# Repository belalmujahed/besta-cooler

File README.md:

# Bestå cooler

Closed-door cooling and lighting for a wall-mounted 3-bay IKEA Bestå TV unit: floor-mounted PWM fans in printed cassettes, one ESP32-C3 controller per bay, ESPHome firmware.

```
cad/        SolidCraft models + STL/STEP exports
  cassette/   fan flange + bottom scoop (one design, all bays)   ✅ v1
  baffle/     under-unit recirculation baffle                     ⏳
  ps5-riser/  platform lifting the PS5 over its fans              ⏳
  controller-case/ printed enclosure, all connectors outside       ✅ v1
pcb/        KiCad 10 project (controller, built 3×)  schematic ✅  layout ✅ (routed, DRC clean)
firmware/   ESPHome: one YAML + per-bay substitutions             ⏳
docs/       spec notes, pin map, BOM, measurements
```

## Bays
| Bay | Contents | Fans (floor) | Board extras |
|---|---|---|---|
| 1 | Xbox Series X, flat (exhaust left side) | back intake, front exhaust | console VBUS sense |
| 2 | AV receiver, PSU brick, splitter | 1 rear exhaust (2nd header spare) | backlight channel |
| 3 | PS5 launch model, flat, **on a riser over the fans** | front intake, back exhaust | console VBUS sense |

Doors stay closed; no visible vents. Extra passive intake through a shadow gap at the bottom edge of the doors. The baffle strip under the unit (10–15 mm) separates intake from exhaust.

## Mechanical
- **Square cutout (~126 mm) per fan, fan fully recessed in the floor panel** (120×15 mm, e.g. Noctua NF-A12x15 PWM).
- **Through-clamp:** the top flange and bottom scoop sandwich the panel with 4× M3 screws through the fan corners into heat-set inserts. This works on a honeycomb core.
- The same scoop serves intake and exhaust: rotate it 180° so the jets point away from each other.
- Hole placement: ≥40 mm from the back edge, ≥50 mm from side panels and cam fittings.
- PETG/ASA, matte black. Details in [cad/cassette/README.md](cad/cassette/README.md).

## Power
Mean Well GST90A12 (12 V 6.67 A) → 1-to-4 barrel splitter → extension leads → PCB barrel jack on each board. The 4th output is spare, or feeds the backlight directly if it outgrows the board's MOSFET. 5.5 mm centre-positive; **2.1 vs 2.5 mm to be confirmed.** No daisy-chaining, no hub PCB.

## Controller PCB (one design, ×3)
- 5.5 mm barrel jack, PTC fuse, reverse-polarity protection, 12→3.3 V buck (AP63203).
- **ESP32-C3-WROOM-02 module** (JLC-assembled; C3-MINI-1 had no KiCad footprint), USB-C, boot/reset buttons, status LED.
- 2× 4-pin fan headers, **independent PWM per fan** (open-drain 2N7002, inverted), separate tach (10k to 3.3 V), shared high-side P-MOSFET fan power switch (true 0 RPM), on by default at reset.
- **3× DS18B20** (intake, exhaust, ambient) on one 1-Wire bus, 4.7k pull-up. Intake/exhaust probes mount on the cassette probe clip.
- Door reed switch header (internal pull-up, optional TVS).
- **2× 12 V low-side MOSFET channels:** compartment COB strip (~0.6 A) + **plain 12 V white backlight** (fitted on the AVR board). The addressable/level-shifter/5 V LDO block was dropped.
- Optional: console power sense from USB VBUS (Xbox + PS5 boards). SHT31 footprint dropped (the ambient DS18B20 replaces it).
- Full plan, pin map and BOM: [docs/pcb-plan.md](docs/pcb-plan.md).
- M3 mounting holes, all connectors on one edge. 2-layer, solid ground plane.

## Firmware (ESPHome)
Fan duty = max(curve(ΔT exhaust−intake), curve(exhaust absolute)): min at ΔT ≤ 3 °C → 100 % at 12 °C; 100 % if exhaust ≥ 50 °C. Full speed on boot and on any sensor fault. Runs fully without Wi-Fi/HA. Fans off when the console is off and the bay is cool. Door → LED fade on 300 ms / off 1 s, 5 min timeout, HA override. Room temp from HA for monitoring only.

## Open review notes
- 2 oz copper isn't needed at <2 A per board, and it costs more at JLC; 1 oz suggested.
- A ~3 A PTC is generous for <1.5 A of load; a ~1.5 A hold is suggested.
- Console USB ports must be set to **power off in standby** (Xbox: energy-saving mode; PS5: "Supply power to USB ports: Off"), otherwise VBUS sense can't see the console's state.
- ESP32-C3 has no PCNT peripheral. ESPHome's `pulse_counter` falls back to interrupts, which is fine for fan tach.

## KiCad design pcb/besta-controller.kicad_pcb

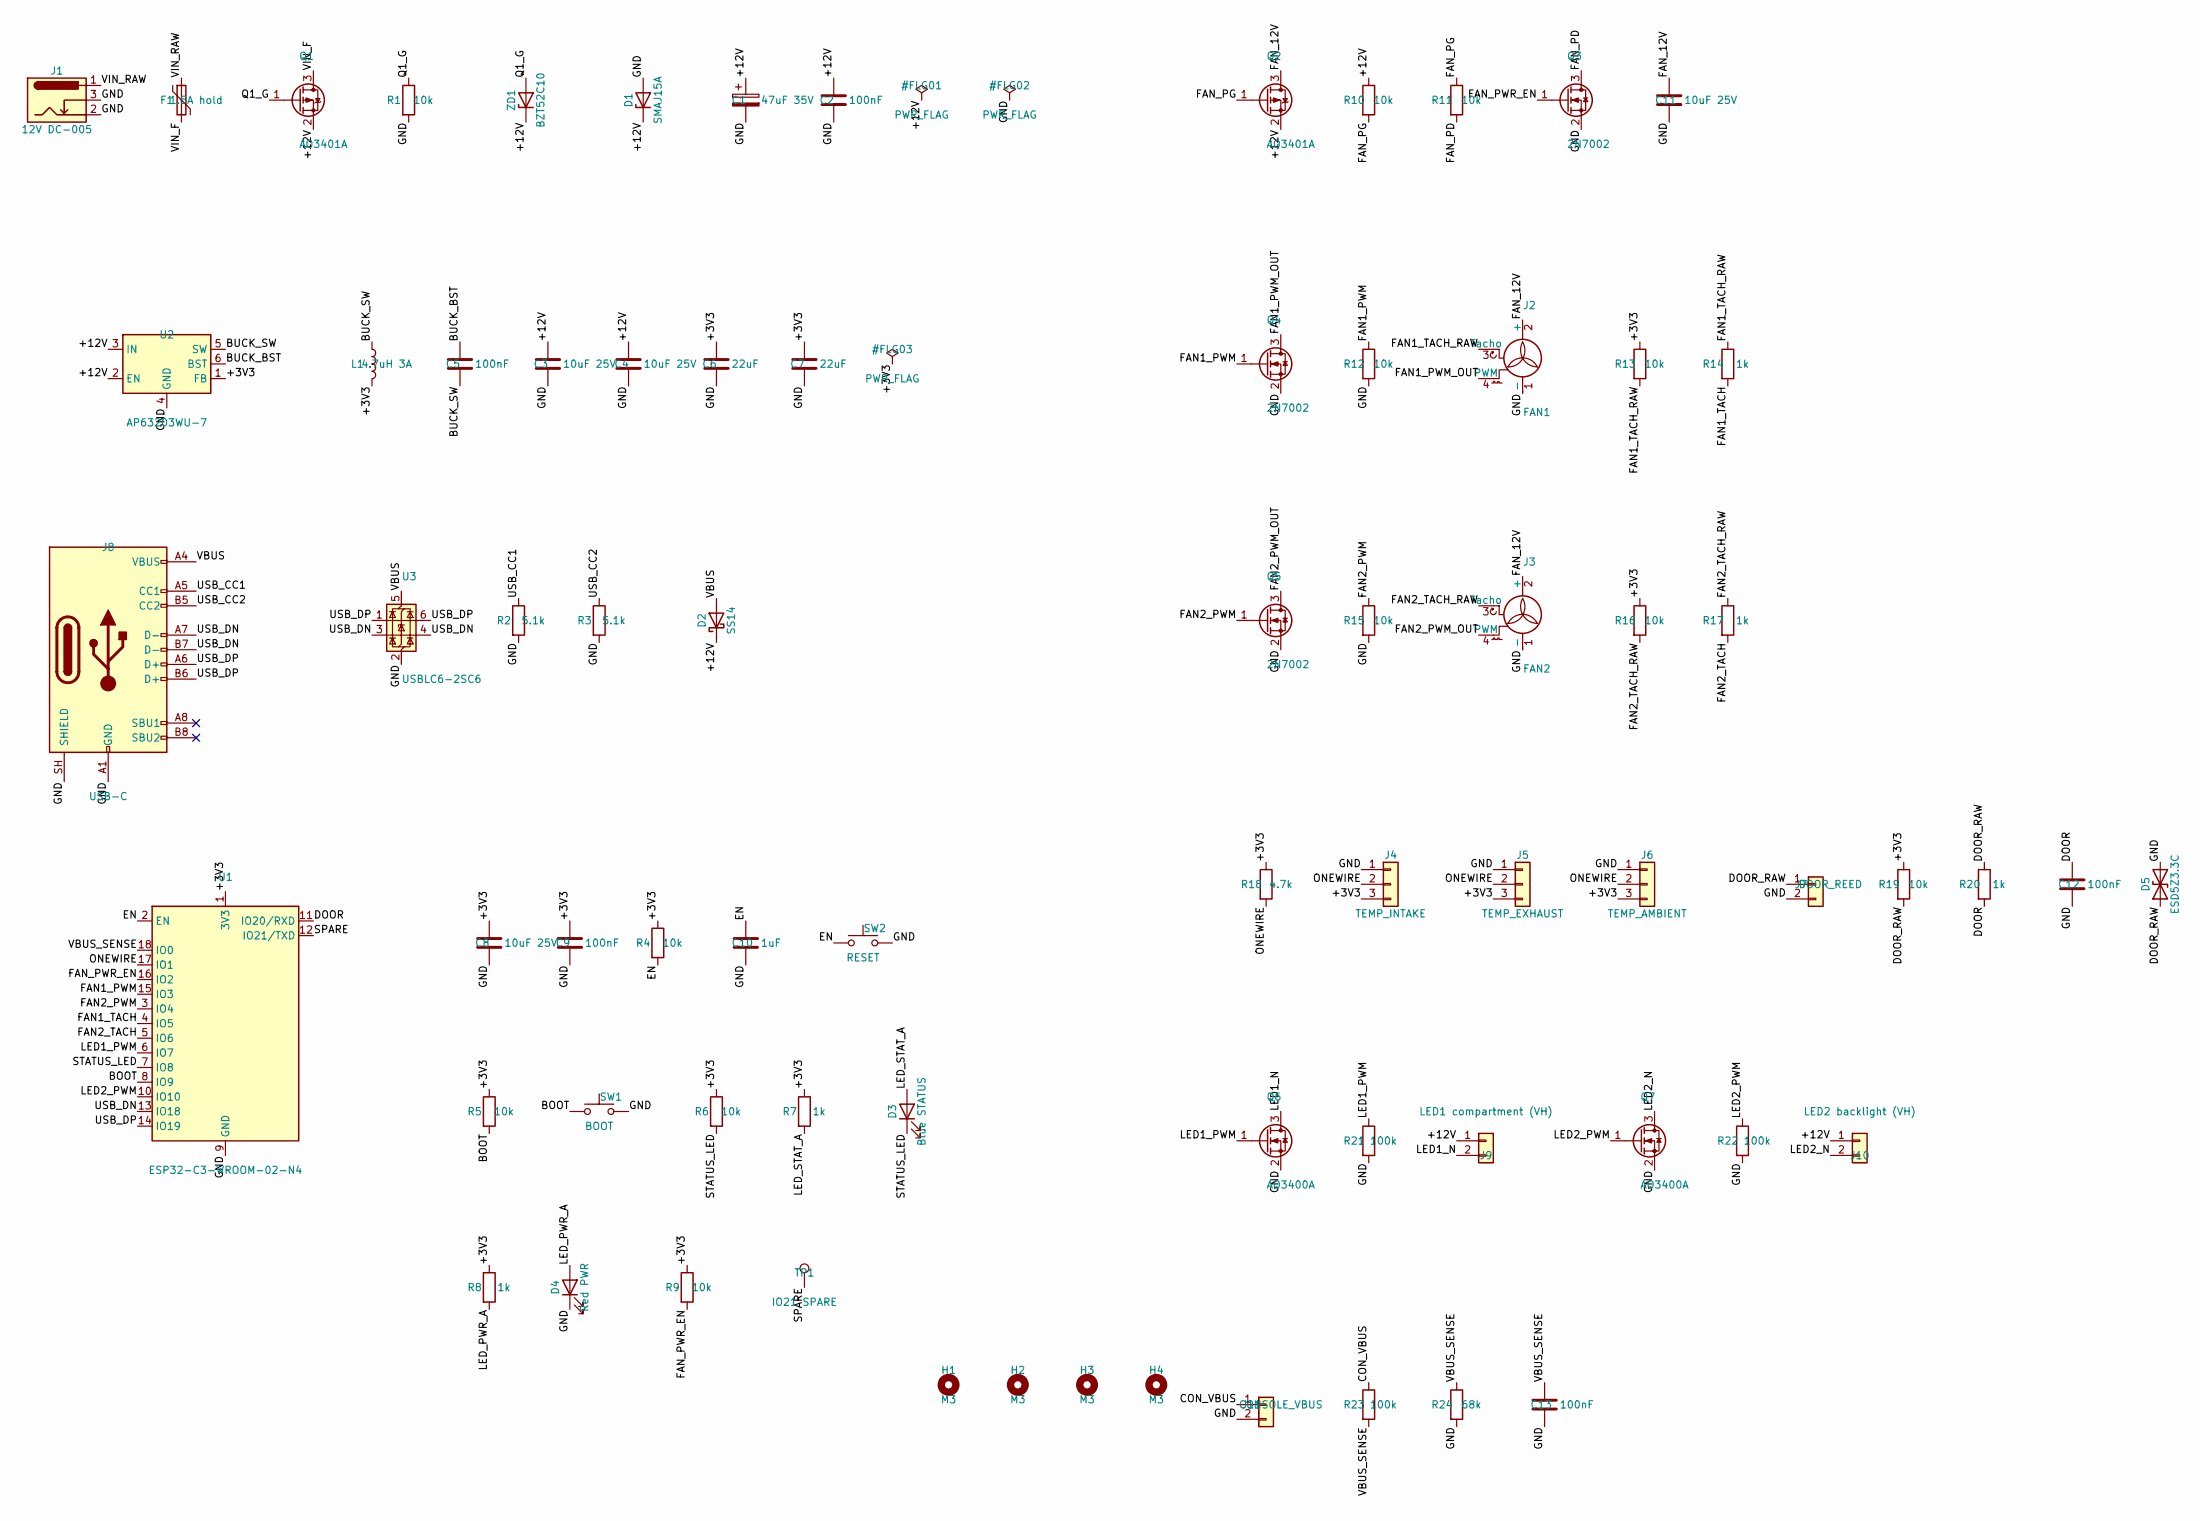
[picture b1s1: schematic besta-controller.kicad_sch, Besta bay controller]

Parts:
C1: 47uF 35V; CP_Elec_6.3x5.4; LCSC C2836440
C2, C5, C9, C12, C13: 100nF; C_0603_1608Metric; LCSC C14663
C3, C4, C8, C11: 10uF 25V; C_0805_2012Metric; LCSC C15850
C6, C7: 22uF; C_0805_2012Metric; LCSC C45783
C10: 1uF; C_0603_1608Metric; LCSC C15849
D1: SMAJ15A; D_SMA; LCSC C19077535
D2: SS14; D_SMA; LCSC C2480
D3: Blue STATUS; LED_0603_1608Metric; LCSC C2288
D4: Red PWR; LED_0603_1608Metric; LCSC C2286
D5: ESD5Z3.3C; D_SOD-523; LCSC C502551
F1: 1.5A hold; Fuse_1812_4532Metric; LCSC C32404
H1, H2, H3, H4: M3; MountingHole_3.2mm_M3
J1: 12V DC-005; BarrelJack_Horizontal; LCSC C720557
J2: FAN1; PinHeader_1x04_P2.54mm_Horizontal; LCSC C2982043
J3: FAN2; PinHeader_1x04_P2.54mm_Horizontal; LCSC C2982043
J4: TEMP_INTAKE; JST_XH_S3B-XH-A_1x03_P2.50mm_Horizontal; LCSC C157928
J5: TEMP_EXHAUST; JST_XH_S3B-XH-A_1x03_P2.50mm_Horizontal; LCSC C157928
J6: TEMP_AMBIENT; JST_XH_S3B-XH-A_1x03_P2.50mm_Horizontal; LCSC C157928
J7: DOOR_REED; JST_XH_S2B-XH-A_1x02_P2.50mm_Horizontal; LCSC C157931
J8: USB-C; USB_C_Receptacle_HRO_TYPE-C-31-M-12; LCSC C165948
J9: LED1 compartment (VH); JST_VH_S2P-VH_1x02_P3.96mm_Horizontal; LCSC C160355
J10: LED2 backlight (VH); JST_VH_S2P-VH_1x02_P3.96mm_Horizontal; LCSC C160355
J11: CONSOLE_VBUS; JST_XH_S2B-XH-A_1x02_P2.50mm_Horizontal; LCSC C157931
L1: 4.7uH 3A; L_Sunlord_SWPA5040S; LCSC C305174
Q1, Q2: AO3401A; SOT-23; LCSC C15127
Q3, Q4, Q5: 2N7002; SOT-23; LCSC C8545
Q6, Q7: AO3400A; SOT-23; LCSC C20917
R1, R4, R5, R6, R9, R10, R11, R12, R13, R15, R16, R19: 10k; R_0603_1608Metric; LCSC C25804
R2, R3: 5.1k; R_0603_1608Metric; LCSC C23186
R7, R8, R14, R17, R20: 1k; R_0603_1608Metric; LCSC C21190
R18: 4.7k; R_0603_1608Metric; LCSC C23162
R21, R22, R23: 100k; R_0603_1608Metric; LCSC C25803
R24: 68k; R_0603_1608Metric; LCSC C114633
SW1: BOOT; SW_Push_1P1T_XKB_TS-1187A; LCSC C318884
SW2: RESET; SW_Push_1P1T_XKB_TS-1187A; LCSC C318884
TP1: IO21 SPARE; TestPoint_Pad_D1.5mm
U1: ESP32-C3-WROOM-02-N4; ESP32-C3-WROOM-02; LCSC C2934560
U2: AP63203WU-7; TSOT-23-6; LCSC C780769
U3: USBLC6-2SC6; SOT-23-6; LCSC C7519
ZD1: BZT52C10; D_SOD-123; LCSC C19077408

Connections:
/+3V3: C6.1, C7.1, C8.1, C9.1, J4.3, J5.3, J6.3, L1.2, R4.1, R5.1, R6.1, R7.1, R8.1, R9.1, R13.1, R16.1, R18.1, R19.1, U1.1 (3V3), U2.1 (FB)
/+12V: C1.1, C2.1, C3.1, C4.1, D1.1 (K), D2.1 (K), J9.1, J10.1, Q1.2 (S), Q2.2 (S), R10.1, U2.2 (EN), U2.3 (IN), ZD1.1 (K)
/BOOT: R5.2, SW1.1, U1.8 (IO9)
/BUCK_BST: C5.1, U2.6 (BST)
/BUCK_SW: C5.2, L1.1, U2.5 (SW)
/CON_VBUS: J11.1, R23.1
/DOOR: C12.1, R20.2, U1.11 (IO20/RXD)
/DOOR_RAW: D5.1 (A1), J7.1, R19.2, R20.1
/EN: C10.1, R4.2, SW2.1, U1.2 (EN)
/FAN1_PWM: Q4.1 (G), R12.1, U1.15 (IO3)
/FAN1_PWM_OUT: J2.4 (PWM), Q4.3 (D)
/FAN1_TACH: R14.2, U1.4 (IO5)
/FAN1_TACH_RAW: J2.3 (Tacho), R13.2, R14.1
/FAN2_PWM: Q5.1 (G), R15.1, U1.3 (IO4)
/FAN2_PWM_OUT: J3.4 (PWM), Q5.3 (D)
/FAN2_TACH: R17.2, U1.5 (IO6)
/FAN2_TACH_RAW: J3.3 (Tacho), R16.2, R17.1
/FAN_12V: C11.1, J2.2 (+), J3.2 (+), Q2.3 (D)
/FAN_PD: Q3.3 (D), R11.2
/FAN_PG: Q2.1 (G), R10.2, R11.1
/FAN_PWR_EN: Q3.1 (G), R9.2, U1.16 (IO2)
/GND: C1.2, C2.2, C3.2, C4.2, C6.2, C7.2, C8.2, C9.2, C10.2, C11.2, C12.2, C13.2, D1.2 (A), D4.1 (K), D5.2 (A2), J1.2, J1.3, J2.1 (-), J3.1 (-), J4.1, J5.1, J6.1, J7.2, J8.A1 (GND), J8.A12 (GND), J8.B1 (GND), J8.B12 (GND), J8.SH (SHIELD), J11.2, Q3.2 (S), Q4.2 (S), Q5.2 (S), Q6.2 (S), Q7.2 (S), R1.2, R2.2, R3.2, R12.2, R15.2, R21.2, R22.2, R24.2, SW1.2, SW2.2, U1.9 (GND), U1.19 (GND), U2.4 (GND), U3.2 (GND)
/LED1_N: J9.2, Q6.3 (D)
/LED1_PWM: Q6.1 (G), R21.1, U1.6 (IO7)
/LED2_N: J10.2, Q7.3 (D)
/LED2_PWM: Q7.1 (G), R22.1, U1.10 (IO10)
/LED_PWR_A: D4.2 (A), R8.2
/LED_STAT_A: D3.2 (A), R7.2
/ONEWIRE: J4.2, J5.2, J6.2, R18.2, U1.17 (IO1)
/Q1_G: Q1.1 (G), R1.1, ZD1.2 (A)
/SPARE: TP1.1, U1.12 (IO21/TXD)
/STATUS_LED: D3.1 (K), R6.2, U1.7 (IO8)
/USB_CC1: J8.A5 (CC1), R2.1
/USB_CC2: J8.B5 (CC2), R3.1
/USB_DN: J8.A7 (D-), J8.B7 (D-), U1.13 (IO18), U3.3 (I/O2), U3.4 (I/O2)
/USB_DP: J8.A6 (D+), J8.B6 (D+), U1.14 (IO19), U3.1 (I/O1), U3.6 (I/O1)
/VBUS: D2.2 (A), J8.A4 (VBUS), J8.A9 (VBUS), J8.B4 (VBUS), J8.B9 (VBUS), U3.5 (VBUS)
/VBUS_SENSE: C13.1, R23.2, R24.1, U1.18 (IO0)
/VIN_F: F1.2, Q1.3 (D)
/VIN_RAW: F1.1, J1.1

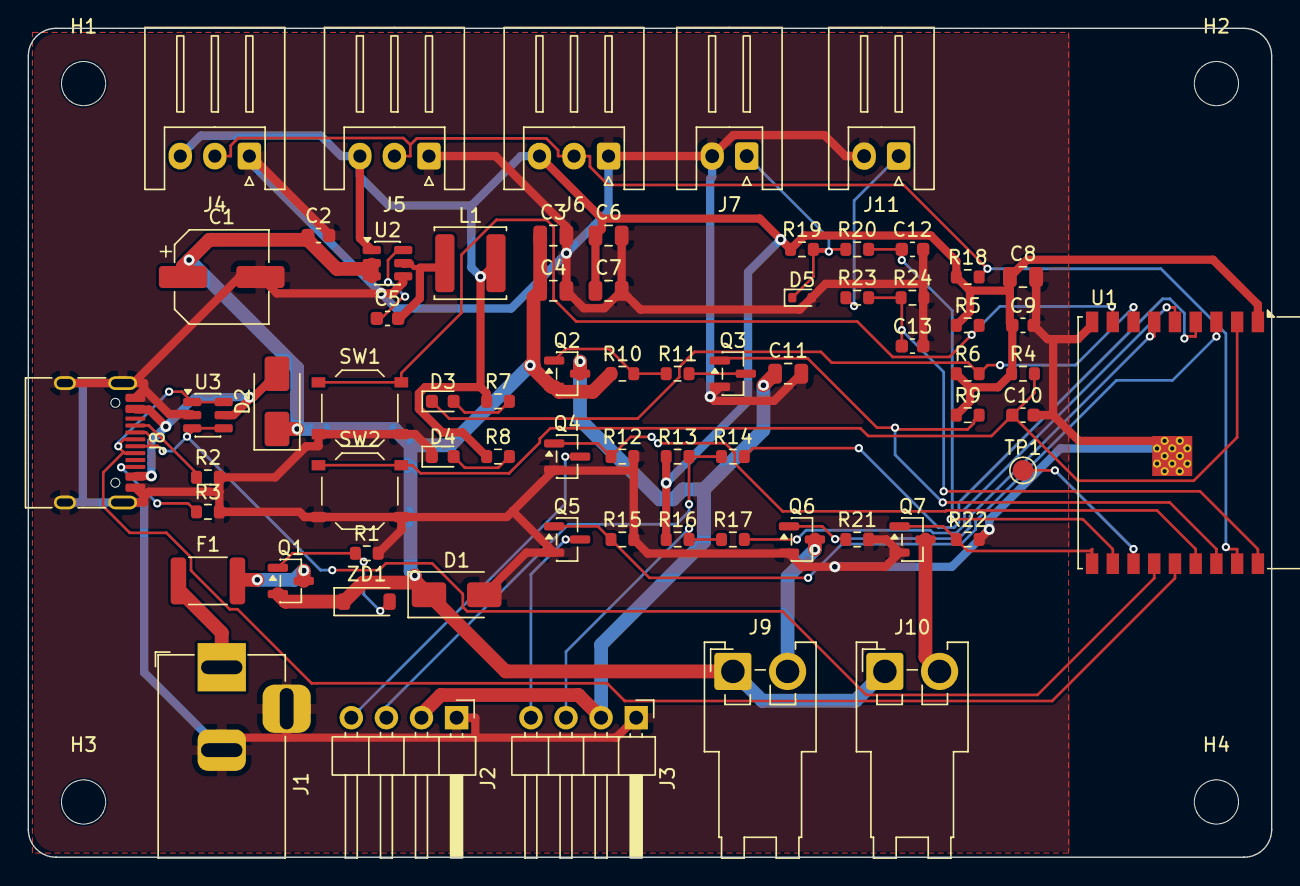
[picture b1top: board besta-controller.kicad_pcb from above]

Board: 2 copper layers, 90.0 x 60.0 mm, 73 parts (0 on the bottom side), 40 nets.

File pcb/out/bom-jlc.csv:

"Comment","Designator","Footprint","LCSC Part #","Qty"
"47uF 35V","C1","Capacitor_SMD:CP_Elec_6.3x5.4","C2836440","1"
"100nF","C2,C5,C9,C12,C13","Capacitor_SMD:C_0603_1608Metric","C14663","5"
"10uF 25V","C3,C4,C8,C11","Capacitor_SMD:C_0805_2012Metric","C15850","4"
"22uF","C6,C7","Capacitor_SMD:C_0805_2012Metric","C45783","2"
"1uF","C10","Capacitor_SMD:C_0603_1608Metric","C15849","1"
"SMAJ15A","D1","Diode_SMD:D_SMA","C19077535","1"
"SS14","D2","Diode_SMD:D_SMA","C2480","1"
"Blue STATUS","D3","LED_SMD:LED_0603_1608Metric","C2288","1"
"Red PWR","D4","LED_SMD:LED_0603_1608Metric","C2286","1"
"ESD5Z3.3C","D5","Diode_SMD:D_SOD-523","C502551","1"
"1.5A hold","F1","Fuse:Fuse_1812_4532Metric","C32404","1"
"M3","H1-H4","MountingHole:MountingHole_3.2mm_M3","","4"
"12V DC-005","J1","Connector_BarrelJack:BarrelJack_Horizontal","C720557","1"
"FAN1","J2","Connector_PinHeader_2.54mm:PinHeader_1x04_P2.54mm_Horizontal","C2982043","1"
"FAN2","J3","Connector_PinHeader_2.54mm:PinHeader_1x04_P2.54mm_Horizontal","C2982043","1"
"TEMP_INTAKE","J4","Connector_JST:JST_XH_S3B-XH-A_1x03_P2.50mm_Horizontal","C157928","1"
"TEMP_EXHAUST","J5","Connector_JST:JST_XH_S3B-XH-A_1x03_P2.50mm_Horizontal","C157928","1"
"TEMP_AMBIENT","J6","Connector_JST:JST_XH_S3B-XH-A_1x03_P2.50mm_Horizontal","C157928","1"
"DOOR_REED","J7","Connector_JST:JST_XH_S2B-XH-A_1x02_P2.50mm_Horizontal","C157931","1"
"USB-C","J8","Connector_USB:USB_C_Receptacle_HRO_TYPE-C-31-M-12","C165948","1"
"LED1 compartment (VH)","J9","Connector_JST:JST_VH_S2P-VH_1x02_P3.96mm_Horizontal","C160355","1"
"LED2 backlight (VH)","J10","Connector_JST:JST_VH_S2P-VH_1x02_P3.96mm_Horizontal","C160355","1"
"CONSOLE_VBUS","J11","Connector_JST:JST_XH_S2B-XH-A_1x02_P2.50mm_Horizontal","C157931","1"
"4.7uH 3A","L1","Inductor_SMD:L_Sunlord_SWPA5040S","C305174","1"
"AO3401A","Q1,Q2","Package_TO_SOT_SMD:SOT-23","C15127","2"
"2N7002","Q3-Q5","Package_TO_SOT_SMD:SOT-23","C8545","3"
"AO3400A","Q6,Q7","Package_TO_SOT_SMD:SOT-23","C20917","2"
"10k","R1,R4-R6,R9-R13,R15,R16,R19","Resistor_SMD:R_0603_1608Metric","C25804","12"
"5.1k","R2,R3","Resistor_SMD:R_0603_1608Metric","C23186","2"
"1k","R7,R8,R14,R17,R20","Resistor_SMD:R_0603_1608Metric","C21190","5"
"4.7k","R18","Resistor_SMD:R_0603_1608Metric","C23162","1"
"100k","R21-R23","Resistor_SMD:R_0603_1608Metric","C25803","3"
"68k","R24","Resistor_SMD:R_0603_1608Metric","C114633","1"
"BOOT","SW1","Button_Switch_SMD:SW_Push_1P1T_XKB_TS-1187A","C318884","1"
"RESET","SW2","Button_Switch_SMD:SW_Push_1P1T_XKB_TS-1187A","C318884","1"
"IO21 SPARE","TP1","TestPoint:TestPoint_Pad_D1.5mm","","1"
"ESP32-C3-WROOM-02-N4","U1","RF_Module:ESP32-C3-WROOM-02","C2934560","1"
"AP63203WU-7","U2","Package_TO_SOT_SMD:TSOT-23-6","C780769","1"
"USBLC6-2SC6","U3","Package_TO_SOT_SMD:SOT-23-6","C7519","1"
"BZT52C10","ZD1","Diode_SMD:D_SOD-123","C19077408","1"
